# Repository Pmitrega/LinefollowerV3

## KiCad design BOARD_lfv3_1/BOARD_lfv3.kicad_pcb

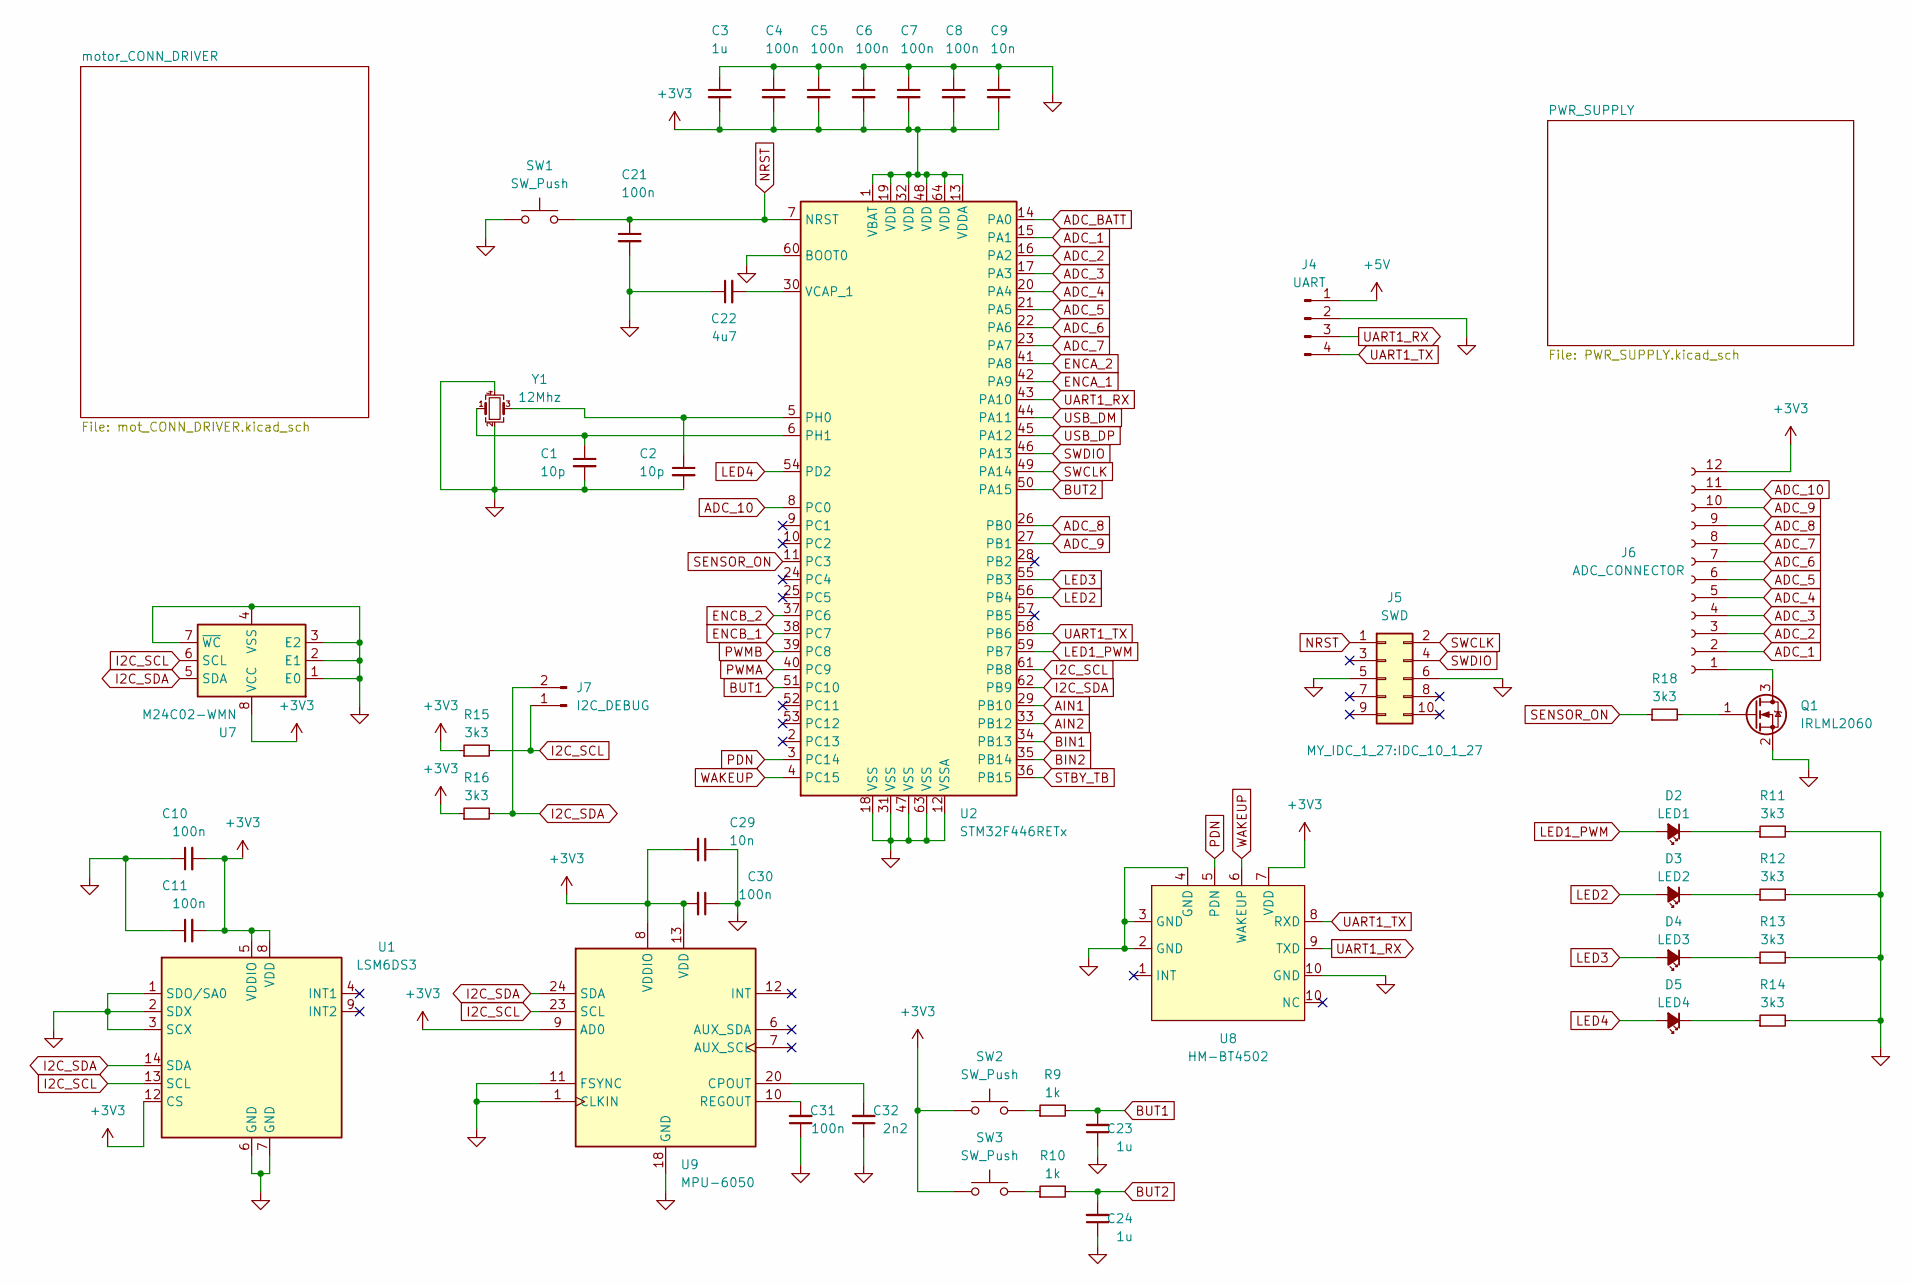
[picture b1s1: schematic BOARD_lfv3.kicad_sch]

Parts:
C1, C2: 10p; C_0603_1608Metric_Pad1.08x0.95mm_HandSolder
C3, C23, C24: 1u; C_0603_1608Metric_Pad1.08x0.95mm_HandSolder
C4, C5, C6, C7, C8, C10, C11, C21, C30, C31: 100n; C_0603_1608Metric_Pad1.08x0.95mm_HandSolder
C9, C29: 10n; C_0603_1608Metric_Pad1.08x0.95mm_HandSolder
C22: 4u7; C_0603_1608Metric_Pad1.08x0.95mm_HandSolder
C32: 2n2; C_0603_1608Metric_Pad1.08x0.95mm_HandSolder
D2: LED1; LED_0603_1608Metric_Pad1.05x0.95mm_HandSolder
D3: LED2; LED_0603_1608Metric_Pad1.05x0.95mm_HandSolder
D4: LED3; LED_0603_1608Metric_Pad1.05x0.95mm_HandSolder
D5: LED4; LED_0603_1608Metric_Pad1.05x0.95mm_HandSolder
J4: UART; PinSocket_1x04_P2.54mm_Vertical
J5: SWD; IDC_10_1_27
J6: ADC_CONNECTOR; Hirose_FH12-12S-0.5SH_1x12-1MP_P0.50mm_Horizontal
J7: I2C_DEBUG; PinHeader_1x02_P2.54mm_Vertical
Q1: IRLML2060; SOT-23
R9, R10: 1k; R_0603_1608Metric_Pad0.98x0.95mm_HandSolder
R11, R12, R13, R14, R15, R16, R18: 3k3; R_0603_1608Metric_Pad0.98x0.95mm_HandSolder
SW1, SW2, SW3: SW_Push; SW_SPST_TL3342
U1: LSM6DS3; LGA-14_3x2.5mm_P0.5mm_LayoutBorder3x4y
U2: STM32F446RETx; LQFP-64_10x10mm_P0.5mm
U7: M24C02-WMN; SOIC-8_3.9x4.9mm_P1.27mm
U8: HM-BT4502; HM-BT4502_kopia
U9: MPU-6050; InvenSense_QFN-24_4x4mm_P0.5mm
Y1: 12Mhz; Crystal_SMD_3225-4Pin_3.2x2.5mm_HandSoldering

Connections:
+3V3: C3.2, C4.2, C5.2, C6.2, C7.2, C8.2, C9.2, C10.2, C11.2, C29.2, C30.2, J6.12, R15.1, R16.1, SW2.1, SW3.1, U1.5 (VDDIO), U1.8 (VDD), U1.12 (CS), U2.1 (VBAT), U2.13 (VDDA), U2.19 (VDD), U2.32 (VDD), U2.48 (VDD), U2.64 (VDD), U7.8 (VCC), U8.7 (VDD), U9.8 (VDDIO), U9.9 (AD0), U9.13 (VDD); also elsewhere on the board
+5V: J4.1; also elsewhere on the board
ADC_1: J6.2, U2.15 (PA1)
ADC_2: J6.3, U2.16 (PA2)
ADC_3: J6.4, U2.17 (PA3)
ADC_4: J6.5, U2.20 (PA4)
ADC_5: J6.6, U2.21 (PA5)
ADC_6: J6.7, U2.22 (PA6)
ADC_7: J6.8, U2.23 (PA7)
ADC_8: J6.9, U2.26 (PB0)
ADC_9: J6.10, U2.27 (PB1)
ADC_10: J6.11, U2.8 (PC0)
ADC_BATT: U2.14 (PA0); also elsewhere on the board
AIN1: U2.29 (PB10); also elsewhere on the board
AIN2: U2.33 (PB12); also elsewhere on the board
BIN1: U2.34 (PB13); also elsewhere on the board
BIN2: U2.35 (PB14); also elsewhere on the board
BUT1: C23.2, R9.2, U2.51 (PC10)
BUT2: C24.2, R10.2, U2.50 (PA15)
ENCA_1: U2.42 (PA9); also elsewhere on the board
ENCA_2: U2.41 (PA8); also elsewhere on the board
ENCB_1: U2.38 (PC7); also elsewhere on the board
ENCB_2: U2.37 (PC6); also elsewhere on the board
GND: C1.2, C2.2, C3.1, C4.1, C5.1, C6.1, C7.1, C8.1, C9.1, C10.1, C11.1, C21.2, C22.1, C23.1, C24.1, C29.1, C30.1, C31.1, C32.1, J4.2, J5.5, J5.6, Q1.2 (S), R11.2, R12.2, R13.2, R14.2, SW1.1, U1.1 (SDO/SA0), U1.2 (SDX), U1.3 (SCX), U1.6 (GND), U1.7 (GND), U2.12 (VSSA), U2.18 (VSS), U2.31 (VSS), U2.47 (VSS), U2.60 (BOOT0), U2.63 (VSS), U7.1 (E0), U7.2 (E1), U7.3 (E2), U7.4 (VSS), U7.7 (~WC), U8.2 (GND), U8.3 (GND), U8.4 (GND), U8.10 (GND), U9.1 (CLKIN), U9.11 (FSYNC), U9.18 (GND), Y1.2, Y1.4; also elsewhere on the board
I2C_SCL: J7.1, R15.2, U1.13 (SCL), U2.61 (PB8), U7.6 (SCL), U9.23 (SCL)
I2C_SDA: J7.2, R16.2, U1.14 (SDA), U2.62 (PB9), U7.5 (SDA), U9.24 (SDA)
LED1_PWM: D2.2 (A), U2.59 (PB7)
LED2: D3.2 (A), U2.56 (PB4)
LED3: D4.2 (A), U2.55 (PB3)
LED4: D5.2 (A), U2.54 (PD2)
NRST: C21.1, J5.1, SW1.2, U2.7 (NRST)
unnamed: C1.1, U2.6 (PH1), Y1.1
unnamed: C2.1, U2.5 (PH0), Y1.3
unnamed: C22.2, U2.30 (VCAP_1)
unnamed: C31.2, U9.10 (REGOUT)
unnamed: C32.2, U9.20 (CPOUT)
unnamed: D2.1 (K), R11.1
unnamed: D3.1 (K), R12.1
unnamed: D4.1 (K), R13.1
unnamed: D5.1 (K), R14.1
unnamed: J6.1, Q1.3 (D)
unnamed: Q1.1 (G), R18.2
unnamed: R9.1, SW2.2
unnamed: R10.1, SW3.2
PDN: U2.3 (PC14), U8.5 (PDN)
PWMA: U2.40 (PC9); also elsewhere on the board
PWMB: U2.39 (PC8); also elsewhere on the board
SENSOR_ON: R18.1, U2.11 (PC3)
STBY_TB: U2.36 (PB15); also elsewhere on the board
SWCLK: J5.2, U2.49 (PA14)
SWDIO: J5.4, U2.46 (PA13)
UART1_RX: J4.3, U2.43 (PA10), U8.9 (TXD)
UART1_TX: J4.4, U2.58 (PB6), U8.8 (RXD)
USB_DM: U2.44 (PA11)
USB_DP: U2.45 (PA12)
WAKEUP: U2.4 (PC15), U8.6 (WAKEUP)

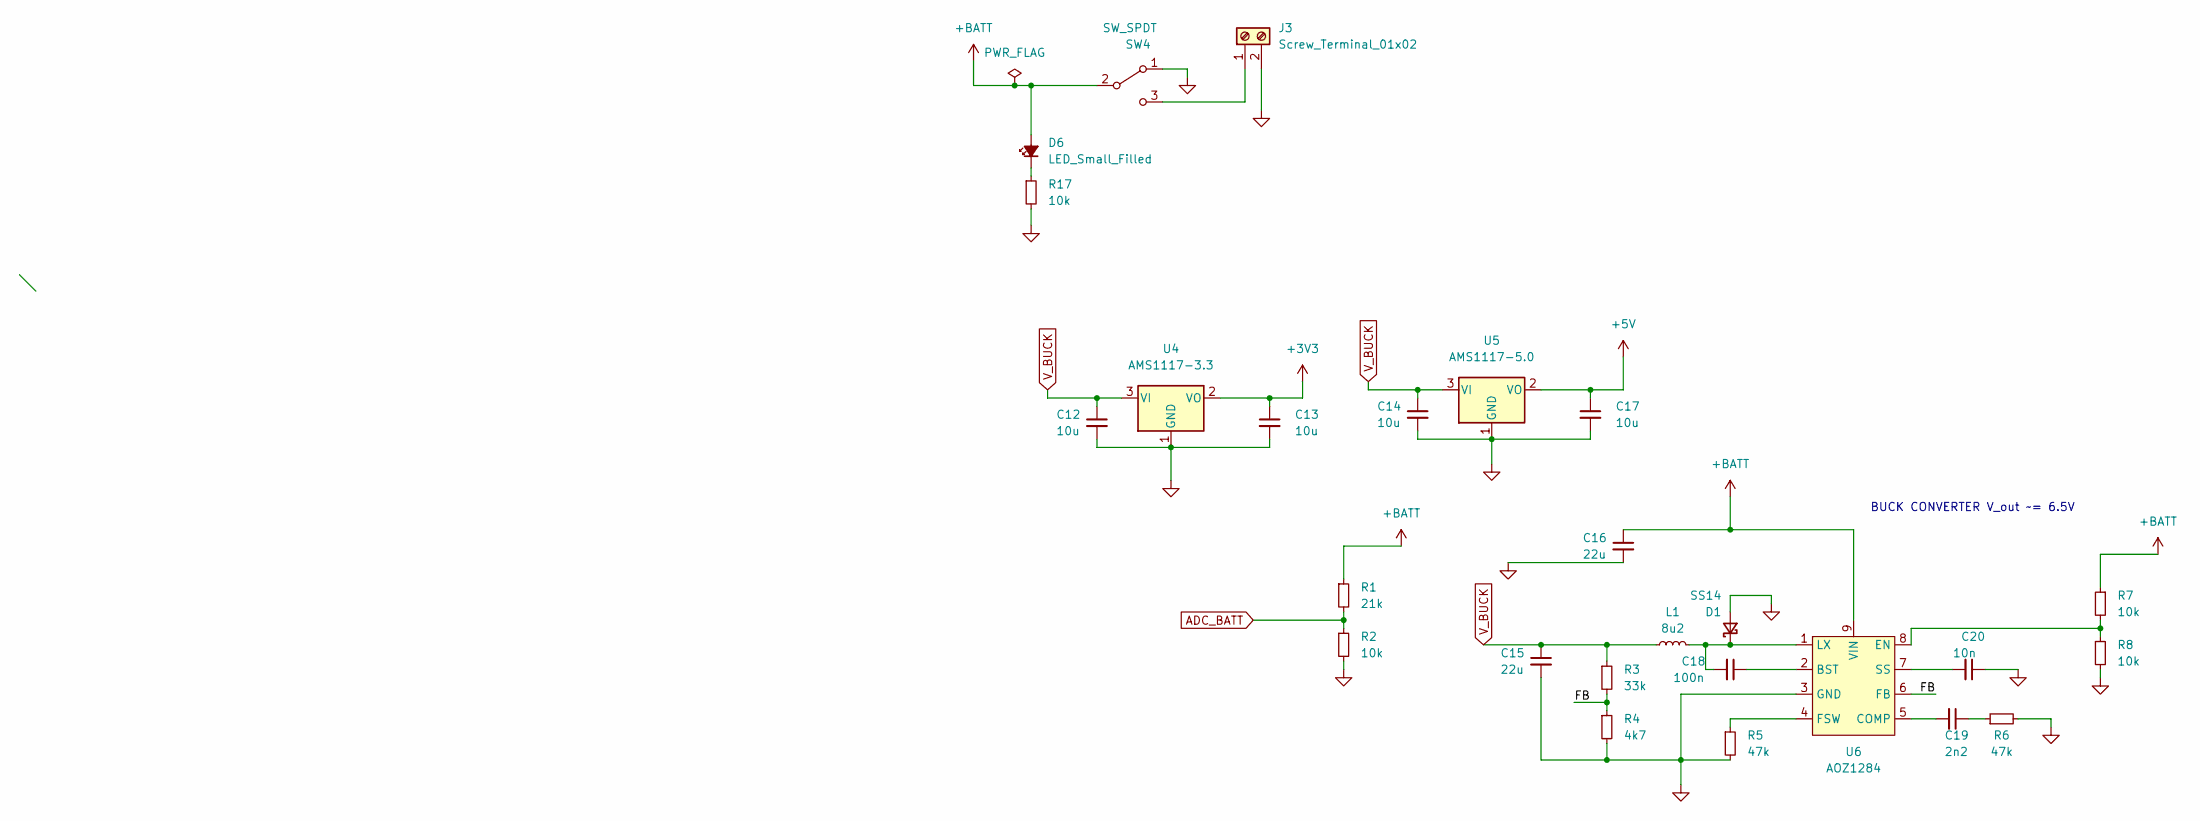
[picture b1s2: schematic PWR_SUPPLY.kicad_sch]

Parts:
C12, C13, C14, C17: 10u; C_0603_1608Metric_Pad1.08x0.95mm_HandSolder
C15, C16: 22u; C_0805_2012Metric_Pad1.18x1.45mm_HandSolder
C18: 100n; C_0603_1608Metric_Pad1.08x0.95mm_HandSolder
C19: 2n2; C_0603_1608Metric_Pad1.08x0.95mm_HandSolder
C20: 10n; C_0603_1608Metric_Pad1.08x0.95mm_HandSolder
D1: SS14; D_SMA_Handsoldering
D6: LED_Small_Filled; LED_0603_1608Metric_Pad1.05x0.95mm_HandSolder
J3: Screw_Terminal_01x02; TerminalBlock_4Ucon_1x02_P3.50mm_Horizontal
L1: 8u2; L_7.3x7.3_H4.5
R1: 21k; R_0603_1608Metric_Pad0.98x0.95mm_HandSolder
R2, R7, R8, R17: 10k; R_0603_1608Metric_Pad0.98x0.95mm_HandSolder
R3: 33k; R_0603_1608Metric_Pad0.98x0.95mm_HandSolder
R4: 4k7; R_0603_1608Metric_Pad0.98x0.95mm_HandSolder
R5, R6: 47k; R_0603_1608Metric_Pad0.98x0.95mm_HandSolder
SW4: SW_SPDT; SS22T20
U4: AMS1117-3.3; SOT-223-3_TabPin2
U5: AMS1117-5.0; SOT-223-3_TabPin2
U6: AOZ1284; SO-8-pad

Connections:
+3V3: C13.1, U4.2 (VO); also elsewhere on the board
+5V: C17.1, U5.2 (VO); also elsewhere on the board
+BATT: C16.1, D6.2 (A), R1.1, R7.1, SW4.2 (B), U6.9 (VIN)
/PWR_SUPPLY/FB: R3.2, R4.1, U6.6 (FB)
ADC_BATT: R1.2, R2.1; also elsewhere on the board
GND: C12.2, C13.2, C14.2, C15.2, C16.2, C17.2, C20.1, D1.2 (A), J3.2, R2.2, R4.2, R5.2, R6.2, R8.2, R17.2, SW4.1 (A), U4.1 (GND), U5.1 (GND), U6.3 (GND); also elsewhere on the board
unnamed: C18.1, U6.2 (BST)
unnamed: C18.2, D1.1 (K), L1.2, U6.1 (LX)
unnamed: C19.1, R6.1
unnamed: C19.2, U6.5 (COMP)
unnamed: C20.2, U6.7 (SS)
unnamed: D6.1 (K), R17.1
unnamed: J3.1, SW4.3 (C)
unnamed: R5.1, U6.4 (FSW)
unnamed: R7.2, R8.1, U6.8 (EN)
V_BUCK: C12.1, C14.1, C15.1, L1.1, R3.1, U4.3 (VI), U5.3 (VI); also elsewhere on the board

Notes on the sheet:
BUCK CONVERTER V_out ~= 6.5V

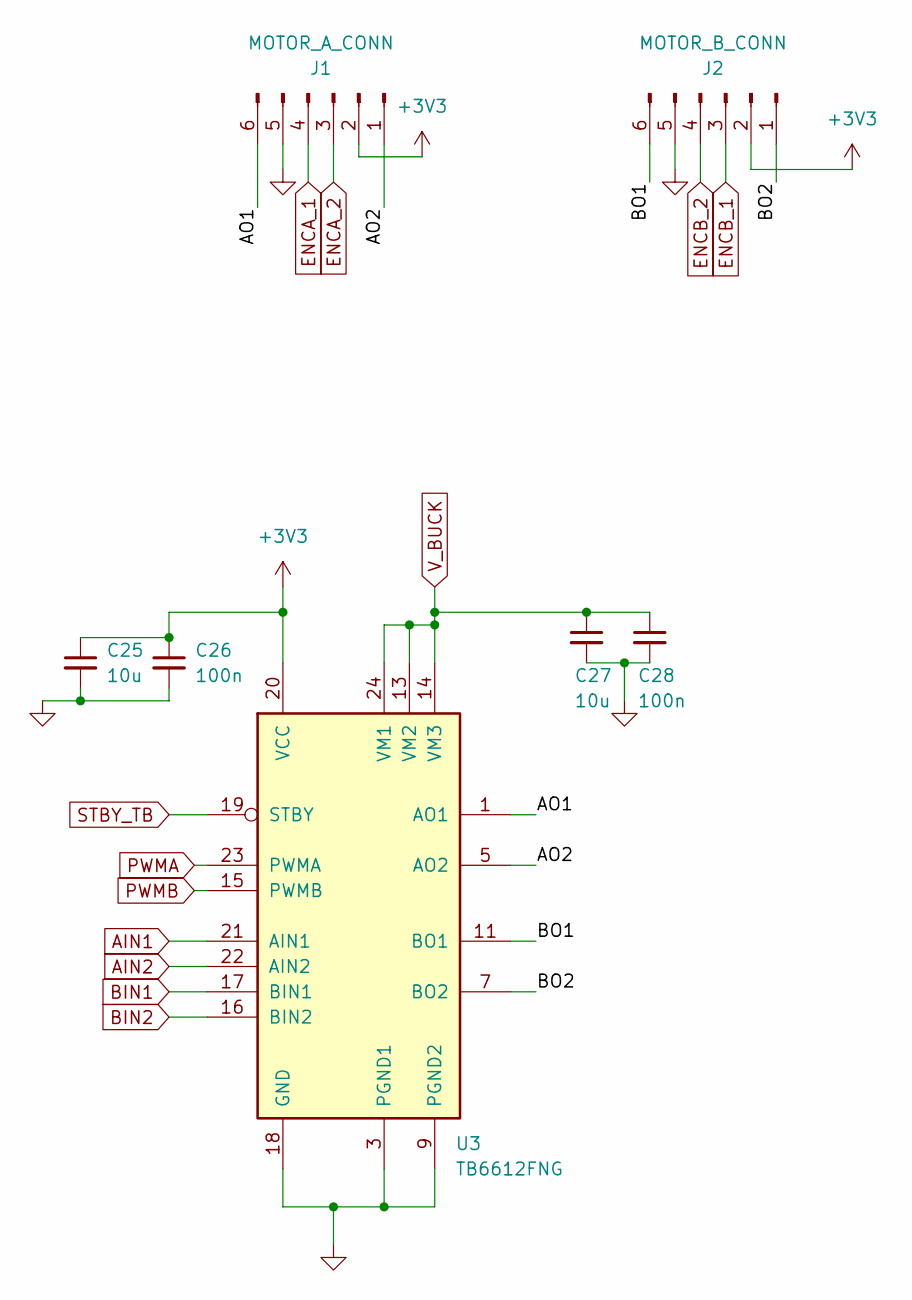
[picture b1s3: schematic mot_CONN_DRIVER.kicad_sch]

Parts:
C25, C27: 10u; C_0805_2012Metric_Pad1.18x1.45mm_HandSolder
C26, C28: 100n; C_0603_1608Metric_Pad1.08x0.95mm_HandSolder
J1: MOTOR_A_CONN; JST_XH_B6B-XH-A_1x06_P2.50mm_Vertical
J2: MOTOR_B_CONN; JST_XH_B6B-XH-A_1x06_P2.50mm_Vertical
U3: TB6612FNG; SSOP-24_5.3x8.2mm_P0.65mm

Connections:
+3V3: C25.1, C26.1, J1.2, J2.2, U3.20 (VCC); also elsewhere on the board
/motor_CONN_DRIVER/AO1: J1.6, U3.1 (AO1), U3.2 (AO1)
/motor_CONN_DRIVER/AO2: J1.1, U3.5 (AO2), U3.6 (AO2)
/motor_CONN_DRIVER/BO1: J2.6, U3.11 (BO1), U3.12 (BO1)
/motor_CONN_DRIVER/BO2: J2.1, U3.7 (BO2), U3.8 (BO2)
AIN1: U3.21 (AIN1); also elsewhere on the board
AIN2: U3.22 (AIN2); also elsewhere on the board
BIN1: U3.17 (BIN1); also elsewhere on the board
BIN2: U3.16 (BIN2); also elsewhere on the board
ENCA_1: J1.4; also elsewhere on the board
ENCA_2: J1.3; also elsewhere on the board
ENCB_1: J2.3; also elsewhere on the board
ENCB_2: J2.4; also elsewhere on the board
GND: C25.2, C26.2, C27.2, C28.2, J1.5, J2.5, U3.3 (PGND1), U3.4 (PGND1), U3.9 (PGND2), U3.10 (PGND2), U3.18 (GND); also elsewhere on the board
PWMA: U3.23 (PWMA); also elsewhere on the board
PWMB: U3.15 (PWMB); also elsewhere on the board
STBY_TB: U3.19 (STBY); also elsewhere on the board
V_BUCK: C27.1, C28.1, U3.13 (VM2), U3.14 (VM3), U3.24 (VM1); also elsewhere on the board

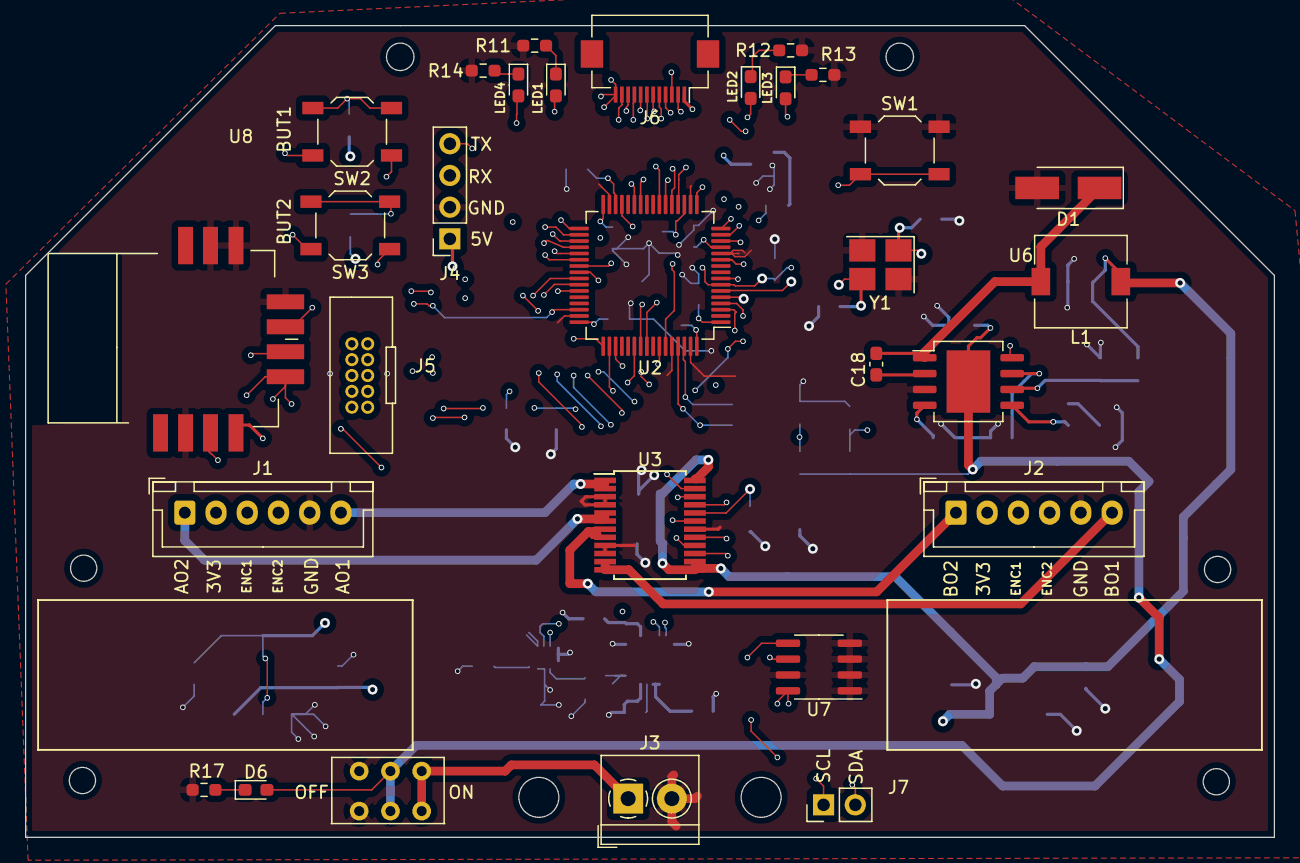
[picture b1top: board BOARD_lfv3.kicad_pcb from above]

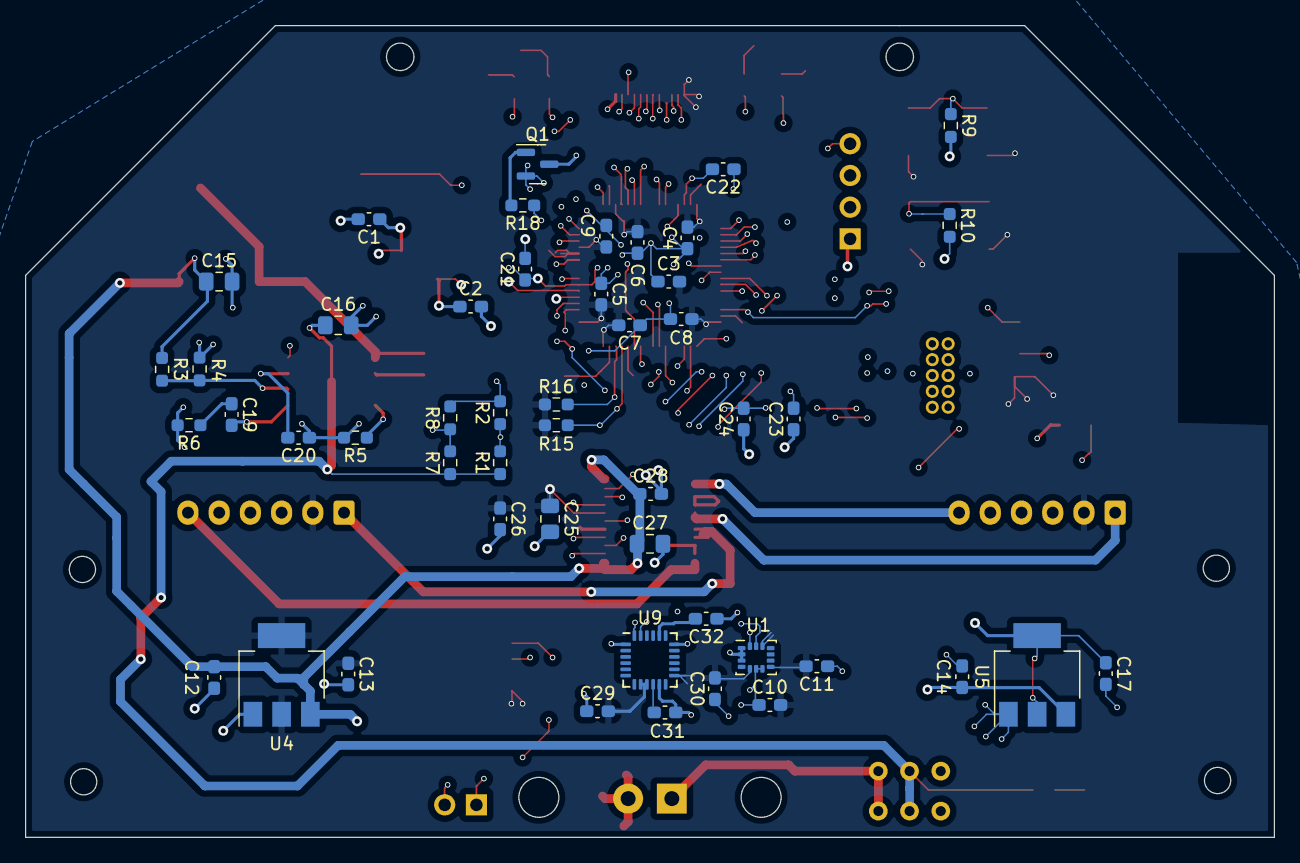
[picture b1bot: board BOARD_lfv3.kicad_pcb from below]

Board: 4 copper layers, 100.0 x 65.0 mm, 79 parts (49 on the bottom side), 70 nets.

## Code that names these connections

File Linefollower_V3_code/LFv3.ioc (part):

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Mcu.Name=STM32F446R(C-E)Tx
Mcu.Package=LQFP64
Mcu.UserName=STM32F446RETx
PA0-WKUP.GPIOParameters=GPIO_Label
PA0-WKUP.GPIO_Label=ADC_BATT
PA0-WKUP.Signal=ADCx_IN0
PA1.Signal=ADCx_IN1
PA10.Mode=Asynchronous
PA10.Signal=USART1_RX
PA13.Mode=Serial_Wire
PA13.Signal=SYS_JTMS-SWDIO
PA14.Mode=Serial_Wire
PA14.Signal=SYS_JTCK-SWCLK
PA15.GPIOParameters=GPIO_PuPd,GPIO_Label
PA15.GPIO_Label=BUT2
PA15.GPIO_PuPd=GPIO_PULLDOWN
PA15.Signal=GPIO_Input
PA2.Signal=ADCx_IN2
PA3.Signal=ADCx_IN3
PA4.Signal=ADCx_IN4
PA5.Signal=ADCx_IN5
PA6.Signal=ADCx_IN6
PA7.Signal=ADCx_IN7
PA8.GPIOParameters=GPIO_Label
PA8.GPIO_Label=ENCA_2
PA8.Signal=S_TIM1_CH1
PA9.GPIOParameters=GPIO_Label
PA9.GPIO_Label=ENCA_1
PA9.Signal=S_TIM1_CH2
PB0.Signal=ADCx_IN8
PB1.Signal=ADCx_IN9
PB10.GPIOParameters=GPIO_Label
PB10.GPIO_Label=AIN1
PB10.Signal=GPIO_Output
PB12.GPIOParameters=GPIO_Label
PB12.GPIO_Label=AIN2
PB12.Signal=GPIO_Output
PB13.GPIOParameters=GPIO_Label
PB13.GPIO_Label=BIN1
PB13.Signal=GPIO_Output
PB14.GPIOParameters=GPIO_Label
PB14.GPIO_Label=BIN2
PB14.Signal=GPIO_Output
PB15.GPIOParameters=GPIO_Label
PB15.GPIO_Label=STBY_TB
PB15.Signal=GPIO_Output
PB3.GPIOParameters=GPIO_Label
PB3.GPIO_Label=LED3
PB3.Signal=GPIO_Output
PB4.GPIOParameters=GPIO_Label
PB4.GPIO_Label=LED2
PB4.Signal=GPIO_Output
PB6.Mode=Asynchronous
PB6.Signal=USART1_TX
PB7.GPIOParameters=GPIO_Label
PB7.GPIO_Label=LED1_PWM
PB7.Signal=S_TIM4_CH2
PB8.Mode=I2C
PB8.Signal=I2C1_SCL
PB9.Mode=I2C
PB9.Signal=I2C1_SDA
PC0.Signal=ADCx_IN10
PC10.GPIOParameters=GPIO_PuPd,GPIO_Label
PC10.GPIO_Label=BUT1
PC10.GPIO_PuPd=GPIO_PULLDOWN
PC10.Signal=GPIO_Input
PC14-OSC32_IN.GPIOParameters=GPIO_Label
PC14-OSC32_IN.GPIO_Label=PDN
PC14-OSC32_IN.Signal=GPIO_Output
PC15-OSC32_OUT.GPIOParameters=GPIO_Label
PC15-OSC32_OUT.GPIO_Label=WAKEUP
PC15-OSC32_OUT.Signal=GPIO_Output
PC3.GPIOParameters=GPIO_Label
PC3.GPIO_Label=SENSOR_ON
PC3.Signal=GPIO_Output
PC6.GPIOParameters=GPIO_Label
PC6.GPIO_Label=ENCB_2
PC6.Signal=S_TIM3_CH1
PC7.GPIOParameters=GPIO_Label
PC7.GPIO_Label=ENCB_1
PC7.Signal=S_TIM3_CH2
PC8.GPIOParameters=GPIO_Label
PC8.GPIO_Label=PWMB
PC8.Signal=S_TIM8_CH3
PC9.GPIOParameters=GPIO_Label
PC9.GPIO_Label=PWMA
PC9.Signal=S_TIM8_CH4
PD2.GPIOParameters=GPIO_Label
PD2.GPIO_Label=LED4
PD2.Signal=GPIO_Output
PH0-OSC_IN.Mode=HSE-External-Oscillator
PH0-OSC_IN.Signal=RCC_OSC_IN
PH1-OSC_OUT.Mode=HSE-External-Oscillator
PH1-OSC_OUT.Signal=RCC_OSC_OUT
RCC.HSE_VALUE=12000000
RCC.SYSCLKFreq_VALUE=180000000
RCC.SYSCLKSource=RCC_SYSCLKSOURCE_PLLCLK
board=custom

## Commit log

2023-09-23 Battery handling
2023-09-23 creating state machine for controlling robot
2023-09-24 created cycylic reading of mpu6050
2023-09-28 added velocity estimation
2023-10-03 PID for motors
2023-10-03 some comments
2023-10-03 fixed uart issue, which prevented writing negative values, battery voltage filtering, motors PID, taken motor characteristic without load.
2023-10-04 added docs foler
2023-10-05 added P linefollowing algorithmt
2023-10-18 added 3d models, PID control for linefollowing and started matlab model
2023-10-22 updated model
2023-11-01 added data loging
2023-11-01 added python script for reading logs
2023-11-01 added leadring NN
2023-11-01 added working NN
2023-11-06 added angle estimation using NN
2023-11-26 updated motor meassurements
